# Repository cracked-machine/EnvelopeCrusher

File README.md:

# EnvelopeCrusher

### TODO

- replace CD4066 with modern quad analog switch IC
- complete layout

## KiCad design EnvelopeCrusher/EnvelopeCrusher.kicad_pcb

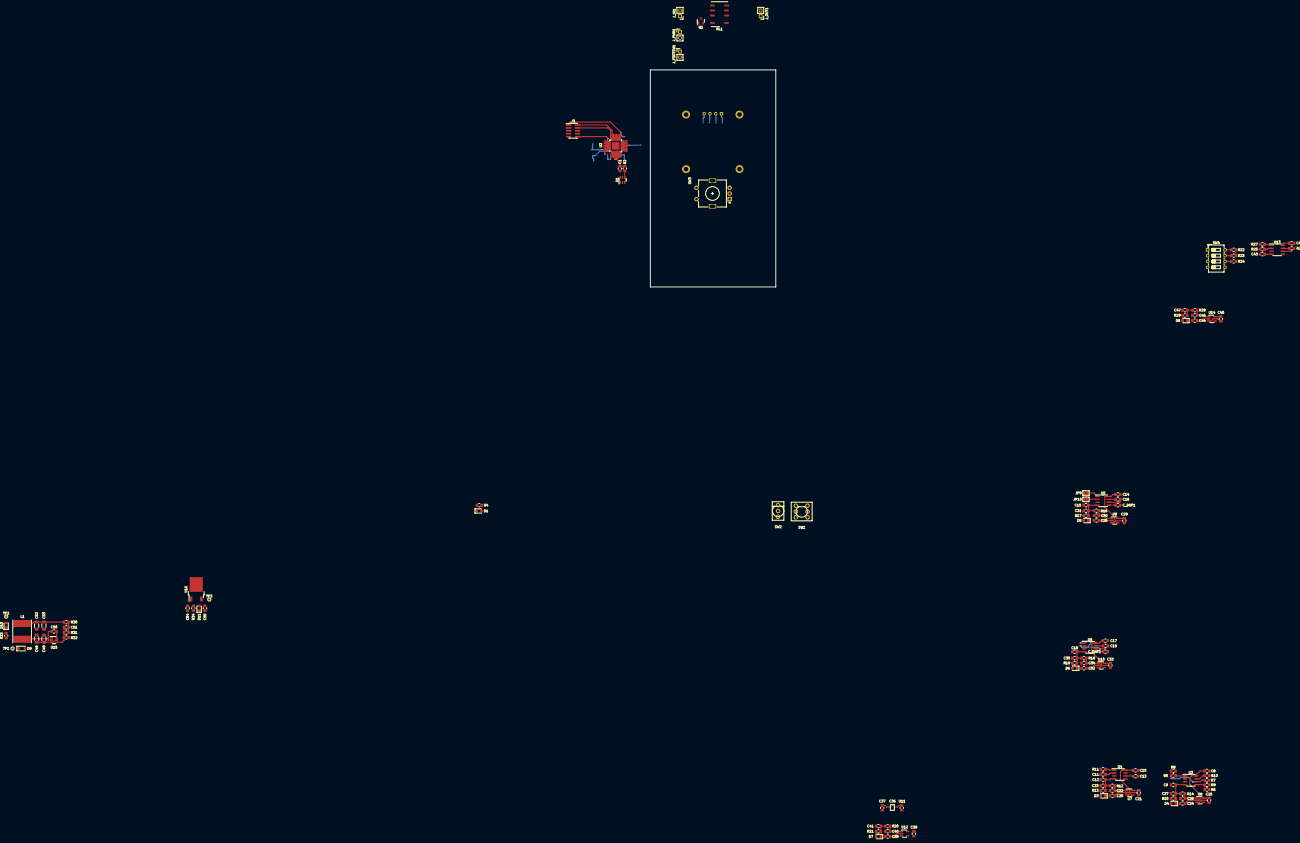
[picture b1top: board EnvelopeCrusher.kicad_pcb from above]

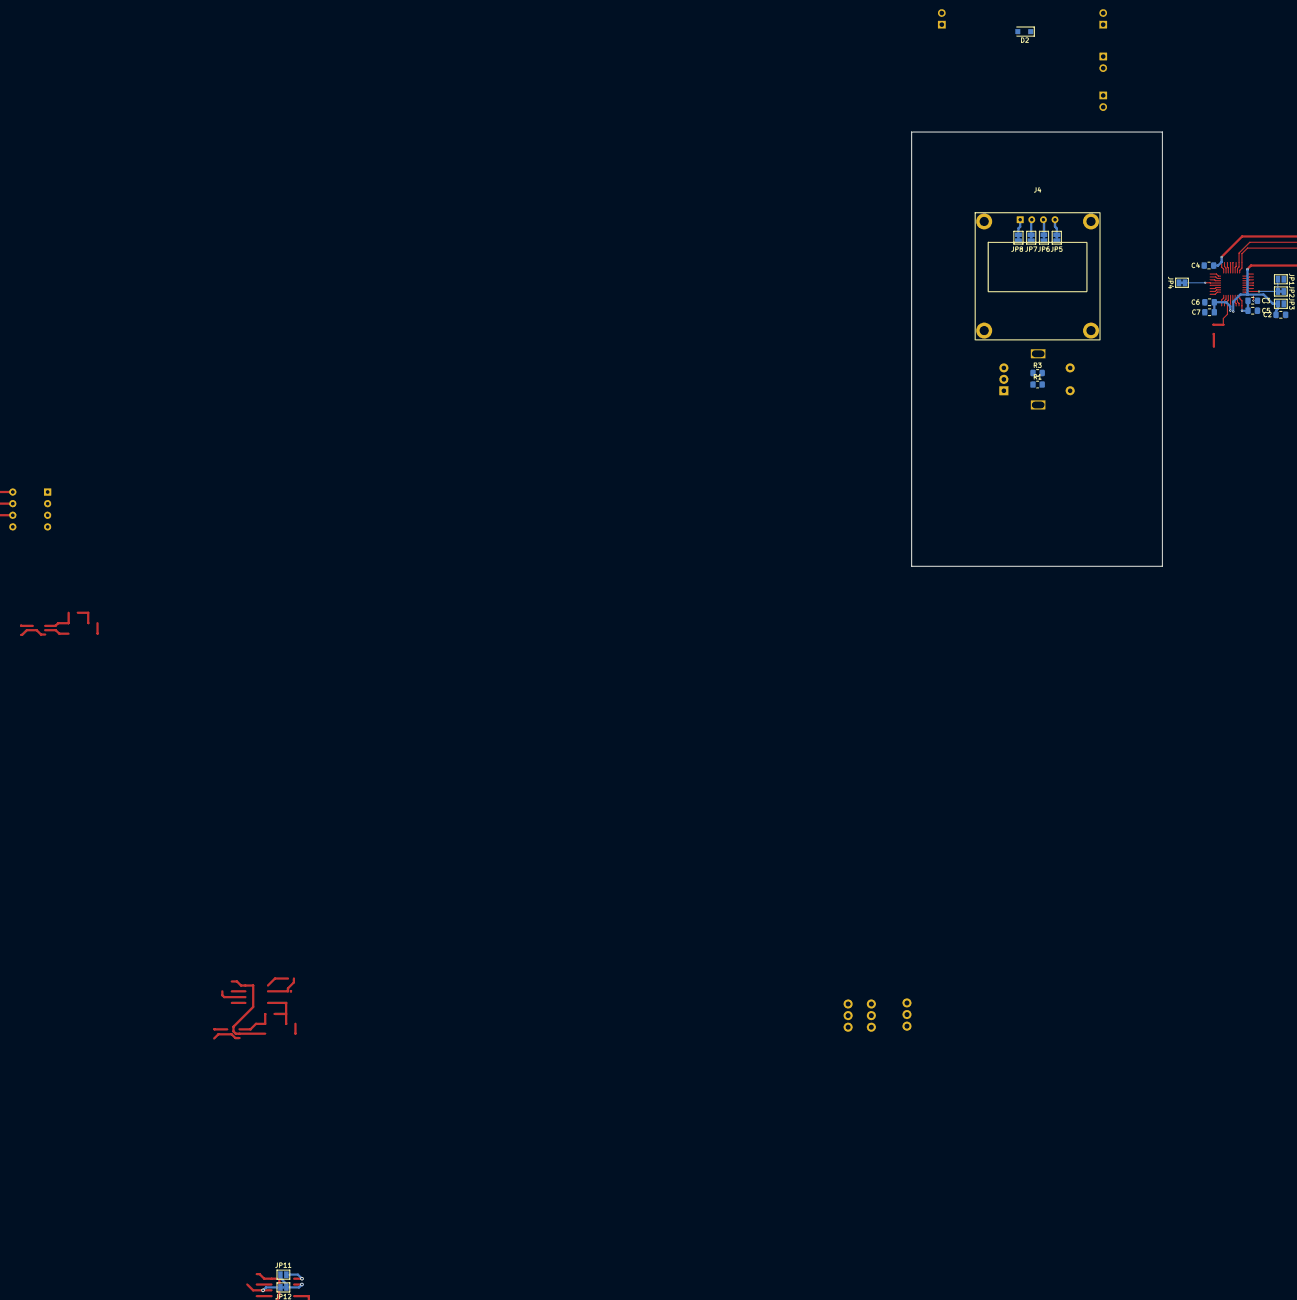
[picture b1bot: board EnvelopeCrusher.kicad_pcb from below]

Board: 2 copper layers, 146 parts (20 on the bottom side), 105 nets.

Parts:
C1, C2, C3, C4, C8, C9, C10, C12, C14, C15, C17, C18, C42, C43, C50: 100nF; C_0805_2012Metric_Pad1.18x1.45mm_HandSolder
C5, C55: 4.7uF; C_0805_2012Metric_Pad1.18x1.45mm_HandSolder
C6, C11, C13: 10nF; C_0805_2012Metric_Pad1.18x1.45mm_HandSolder
C7, C20, C21, C22, C23, C24, C25, C26, C27, C28, C29, C30, C31, C32, C33, C34, C35, C38, C39, C40, C41, C44, C45, C46, C47: 1uF; C_0805_2012Metric_Pad1.18x1.45mm_HandSolder
C16, C19, C36, C37: 1nF; C_0805_2012Metric_Pad1.18x1.45mm_HandSolder
C48: 10uF 20V X5R; R_1206_3216Metric_Pad1.30x1.75mm_HandSolder
C49: 100nF 20V X5R; R_1206_3216Metric_Pad1.30x1.75mm_HandSolder
C51: 75pF; C_0805_2012Metric_Pad1.18x1.45mm_HandSolder
C52, C53: 22uF 10V X5R; R_1206_3216Metric_Pad1.30x1.75mm_HandSolder
C54: 10uF; C_0805_2012Metric_Pad1.18x1.45mm_HandSolder
C_DNF1, C_DNF2: 1nF; C_0805_2012Metric_Pad1.18x1.45mm_HandSolder
D1, D3, D4, D5, D6, D7, D8: LED; LED_0805_2012Metric_Pad1.15x1.40mm_HandSolder
D2: 1n4148; D_SOD-123F
D9: D_Schottky; D_SOD-123F
D10, D11: RED; LED_0805_2012Metric_Pad1.15x1.40mm_HandSolder
J3: Conn_02x05_Odd_Even; PinHeader_2x05_P1.27mm_Vertical_SMD
J4: Conn_01x04; 0.96inch_OLED_SSD1306
JP1, JP3: SolderJumper_2_Open; SolderJumper-2_P1.3mm_Open_Pad1.0x1.5mm
JP2, JP4, JP5, JP6, JP7, JP8: SolderJumper_2_Bridged; SolderJumper-2_P1.3mm_Bridged_Pad1.0x1.5mm
JP9, JP11: Jumper_2_Open; SolderJumper-2_P1.3mm_Open_Pad1.0x1.5mm
JP10, JP12: Jumper_2_Bridged; SolderJumper-2_P1.3mm_Bridged_Pad1.0x1.5mm
J_FOOTSW1: Conn_01x02; PinHeader_1x02_P2.54mm_Vertical
J_IN1: Conn_01x02; PinHeader_1x02_P2.54mm_Vertical
J_OUT1: Conn_01x02; PinHeader_1x02_P2.54mm_Vertical
J_PWR1: Conn_01x02; PinHeader_1x02_P2.54mm_Vertical
L1: 15uH; L_Taiyo-Yuden_NR-80xx_HandSoldering
Q1: Q_NMOS_GSD; SOT-23
R1, R3, R5, R7, R8, R9, R10, R11, R22, R23, R24, R25, R26, R27: 10K; R_0805_2012Metric_Pad1.20x1.40mm_HandSolder
R2, R12, R14, R16, R18, R20, R28: 100R; R_0805_2012Metric_Pad1.20x1.40mm_HandSolder
R4, R13, R15, R17, R19, R21, R29, R33, R34: 2K2; R_0805_2012Metric_Pad1.20x1.40mm_HandSolder
R6: 20K; R_0805_2012Metric_Pad1.20x1.40mm_HandSolder
R30: 47R; R_0805_2012Metric_Pad1.20x1.40mm_HandSolder
R31: 13K; R_0805_2012Metric_Pad1.20x1.40mm_HandSolder
R32: 100K; R_0805_2012Metric_Pad1.20x1.40mm_HandSolder
RL1: HFD4/3-S1; Relay_Fujitsu_FTR-B3S
SW1: SW_DPDT_x2; Dailywell_DPDT
SW2: SW_SPDT; Dailywell_SPDT
SW3: RotaryEncoder_Switch; RotaryEncoder_Alps_EC11E-Switch_Vertical_H20mm
SW4: SW_DIP_x04; SW_DIP_SPSTx04_Slide_6.7x11.72mm_W7.62mm_P2.54mm_LowProfile
TP1, TP2, TP3: TestPoint; TestPoint_Pad_D1.0mm
U1: MCP603-xCH; SOT-23-6
U2: STM32L432KBUx; QFN-32-1EP_5x5mm_P0.5mm_EP3.3x3.3mm_TestPoints
U3, U4, U5, U6, U13: AS358AMTR; SOIC-8_3.9x4.9mm_P1.27mm
U7, U8, U9, U10, U12, U14: TPS60400; SOT-23-5_HandSoldering
U11: DG611E; ThinMiniQFN-16_2.6mm_1.8mm
U15: TPS54202DDC; SOT-23-6
U16: NCV5501TG; TO-252-2

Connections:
+3V3: C3.1, C4.1, C5.1, C6.1, C7.1, C55.1, D11.2 (A), J3.1, JP1.2 (B), JP7.2 (B), Q1.3 (D), R1.1, R3.1, TP3.1, U1.6 (V+), U2.1 (VDD), U2.5 (VDDA), U2.17 (VDD), U16.3 (VO)
+5V: C8.2, C10.2, C14.2, C17.2, C20.1, C24.1, C28.1, C32.1, C36.2, C38.1, C42.2, C44.1, C52.1, C53.1, C54.1, D10.2 (A), L1.2, R30.1, TP2.1, U3.8 (V+), U4.8 (V+), U5.8 (V+), U6.8 (V+), U7.2 (IN), U8.2 (IN), U9.2 (IN), U10.2 (IN), U11.11 (V+), U12.2 (IN), U13.8 (V+), U14.2 (IN), U16.1 (VI)
/AnalogSwitch/1E: SW2.1 (A), U11.15 (IN1)
/AnalogSwitch/1Y: JP9.1 (A), U5.1, U11.1 (S1)
/AnalogSwitch/1Z: C_DNF1.1, U5.5 (+), U11.16 (D1)
/AnalogSwitch/2E: SW2.3 (C), U11.14 (IN2)
/AnalogSwitch/2Y: JP11.1 (A), U6.1, U11.12 (S2)
/AnalogSwitch/2Z: C_DNF2.1, U6.5 (+), U11.13 (D2)
/AnalogSwitch/3E: R27.2, U11.6 (IN4), U11.7 (IN3), U13.1
/AnalogSwitch/3Y: R10.2, U11.9 (S3)
/AnalogSwitch/3Z: C11.1, U4.2 (-), U11.8 (D3)
/AnalogSwitch/4Y: R11.2, U11.4 (S4)
/AnalogSwitch/4Z: C13.1, U4.6 (-), U11.5 (D4)
/AnalogSwitch/NegVoltRail4/NEG_VPP_OUT: C37.2, C41.1, R20.2, R21.1, U11.2 (V-)
/AudioPathSwitching/AUDIO_IN: J_IN1.2, RL1.6
/AudioPathSwitching/AUDIO_OUT: J_OUT1.2, RL1.3
/AudioPathSwitching/POST_FX: C19.2, RL1.4, U6.7
/AudioPathSwitching/PRE_FX: RL1.5, U1.3 (+), U5.3 (+)
/AudioPathSwitching/RELAY_SIGNAL: JP4.1 (A), Q1.1 (G)
/InputBuffer/NegVoltRail3/NEG_VPP_OUT: C15.2, C31.1, R16.2, R17.1, U5.4 (V-)
/InputBuffer/OUT: C16.2, SW1.2 (B), U5.7
/MicroController/BOOT0: JP1.1 (A), JP2.2 (B), U2.31 (PH3)
/MicroController/ENV_CLK_MIX1: R26.2, SW2.2 (B), U13.7
/MicroController/ENV_CLK_MIX/NegVoltRail5/NEG_VPP_OUT: C43.2, C47.1, R28.2, R29.1, U13.4 (V-)
/MicroController/NRST: C2.1, J3.10, JP3.2 (B), U2.4 (NRST)
/MicroController/PA0: C1.1, R2.2, U2.6 (PA0)
/MicroController/PA2: SW4.2, U2.8 (PA2)
/MicroController/PA3: J_FOOTSW1.2, U2.9 (PA3)
/MicroController/PA4: SW4.1, U2.10 (PA4)
/MicroController/PA5: SW4.3, U2.11 (PA5)
/MicroController/PA6: SW4.4, U2.12 (PA6)
/MicroController/PA7: JP4.2 (B), U2.13 (PA7)
/MicroController/PA8: R4.1, U2.18 (PA8)
/MicroController/PA9: JP6.2 (B), U2.19 (PA9)
/MicroController/PA10: JP5.2 (B), U2.20 (PA10)
/MicroController/PA15: R3.2, SW3.B, U2.25 (PA15)
/MicroController/PB3: R1.2, SW3.A, U2.26 (PB3)
/MicroController/PB4: SW3.S1, U2.27 (PB4)
/MicroController/SWCLK: J3.4, U2.24 (PA14)
/MicroController/SWDIO: J3.2, U2.23 (PA13)
/OutputBuffer/IN: SW1.5 (B), U6.3 (+)
/OutputBuffer/NegVoltRail3/NEG_VPP_OUT: C18.2, C35.1, R18.2, R19.1, U6.4 (V-)
/PSU/TPS563200_BUCK_MISC/BUCK_VIN: C48.1, C49.1, D9.1 (K), TP1.1, U15.3 (VIN), U15.5 (EN)
/PSU/VIN: D9.2 (A), J_PWR1.2
/StateVariableFilter/FILTER_IN: SW1.3 (C), U3.3 (+)
/StateVariableFilter/FILTER_OUT: C13.2, R7.2, SW1.6 (C), U4.7
/StateVariableFilter/NegVoltRail1/NEG_VPP_OUT: C9.2, C27.1, R14.2, R15.1, U3.4 (V-)
/StateVariableFilter/NegVoltRail2/NEG_VPP_OUT: C12.2, C23.1, R12.2, R13.1, U4.4 (V-)
GND: C1.2, C2.2, C3.2, C4.2, C5.2, C6.2, C7.2, C8.1, C9.1, C10.1, C12.1, C14.1, C15.1, C17.1, C18.1, C20.2, C22.2, C23.2, C24.2, C26.2, C27.2, C28.2, C30.2, C31.2, C32.2, C34.2, C35.2, C36.1, C37.1, C38.2, C40.2, C41.2, C42.1, C43.1, C44.2, C46.2, C47.2, C_DNF1.2, C_DNF2.2, D1.1 (K), D3.1 (K), D4.1 (K), D5.1 (K), D6.1 (K), D7.1 (K), D8.1 (K), J3.3, J3.5, J3.9, JP2.1 (A), JP3.1 (A), JP8.2 (B), J_FOOTSW1.1, J_IN1.1, J_OUT1.1, J_PWR1.1, R6.1, SW3.C, SW3.S2, U1.2 (V-), U1.5 (~CS), U2.16 (VSS), U2.32 (VSS), U2.33 (VSS), U4.3 (+), U4.5 (+), U7.4 (GND), U8.4 (GND), U9.4 (GND), U10.4 (GND), U11.3 (GND), U12.4 (GND), U13.3 (+), U13.5 (+), U14.4 (GND)
GNDS: C48.2, C49.2, C52.2, C53.2, C54.2, C55.2, R32.2, R33.2, R34.2, U15.1 (GND), U16.2 (GND)
unnamed: C11.2, R9.2, R11.1, U4.1
unnamed: C16.1, JP10.2 (B), U5.6 (-)
unnamed: C19.1, JP12.2 (B), U6.6 (-)
unnamed: C21.1, U7.3 (CFLY-)
unnamed: C21.2, U7.5 (CFLY+)
unnamed: C22.1, R12.1, U7.1 (OUT)
unnamed: C25.1, U8.3 (CFLY-)
unnamed: C25.2, U8.5 (CFLY+)
unnamed: C26.1, R14.1, U8.1 (OUT)
unnamed: C29.1, U9.3 (CFLY-)
unnamed: C29.2, U9.5 (CFLY+)
unnamed: C30.1, R16.1, U9.1 (OUT)
unnamed: C33.1, U10.3 (CFLY-)
unnamed: C33.2, U10.5 (CFLY+)
unnamed: C34.1, R18.1, U10.1 (OUT)
unnamed: C39.1, U12.3 (CFLY-)
unnamed: C39.2, U12.5 (CFLY+)
unnamed: C40.1, R20.1, U12.1 (OUT)
unnamed: C45.1, U14.3 (CFLY-)
unnamed: C45.2, U14.5 (CFLY+)
unnamed: C46.1, R28.1, U14.1 (OUT)
unnamed: C50.1, U15.6 (BOOT)
unnamed: C50.2, L1.1, U15.2 (SW)
unnamed: C51.1, R31.2, R32.1, U15.4 (FB)
unnamed: C51.2, R30.2, R31.1
unnamed: D1.2 (A), R4.2
unnamed: D2.1 (K), Q1.2 (S), RL1.8
unnamed: D2.2 (A), RL1.1
unnamed: D3.2 (A), R13.2
unnamed: D4.2 (A), R15.2
unnamed: D5.2 (A), R17.2
unnamed: D6.2 (A), R19.2
unnamed: D7.2 (A), R21.2
unnamed: D8.2 (A), R29.2
unnamed: D10.1 (K), R33.1
unnamed: D11.1 (K), R34.1
unnamed: J4.1, JP8.1 (A)
unnamed: J4.2, JP7.1 (A)
unnamed: J4.3, JP6.1 (A)
unnamed: J4.4, JP5.1 (A)
unnamed: JP9.2 (B), JP10.1 (A), U5.2 (-)
unnamed: JP11.2 (B), JP12.1 (A), U6.2 (-)
unnamed: R2.1, U1.1, U1.4 (-)
unnamed: R5.1, U3.1, U3.2 (-)
unnamed: R5.2, R7.1, R8.1, U3.6 (-)
unnamed: R6.2, R9.1, U3.5 (+)
unnamed: R8.2, R10.1, U3.7
unnamed: R22.1, SW4.8
unnamed: R22.2, R23.2, R26.1, U13.6 (-)
unnamed: R23.1, SW4.7
unnamed: R24.1, SW4.6
unnamed: R24.2, R25.2, R27.1, U13.2 (-)
unnamed: R25.1, SW4.5
unnamed: RL1.2, RL1.7
unnamed: SW1.1 (A), SW1.4 (A)

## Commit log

2022-06-27 Added blocks from RevA
2022-06-27 updated signal path
2022-06-27 Add routing
2022-06-27 REARRANGED BLOCK DIAGRAM AND ROUTING
2022-07-05 Completed Schematic
2022-07-05 Updated schematic
    - Replaced CD4066 (SOIC14) with DG611 (QFN16)
    - Replaced CLK/ENV mixer jumpers with 4xSPST DIPSW
2022-07-07 updated schematic
    - Added values and comments to state-variable filter block
    - Updated footprints
    - Changed Dual Op Amp: TL072 to AM358
2022-07-16 started layout
2022-07-16 Updated footprints/symbol mappings
2022-07-20 organised layout into functional blocks
